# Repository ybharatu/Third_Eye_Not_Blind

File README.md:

# Third_Eye_Not_Blind 
Senior Design

Authors:
  - Yash Bharatula
  - Kyla Hayes
  - Michael Toner
- Alex Symanski

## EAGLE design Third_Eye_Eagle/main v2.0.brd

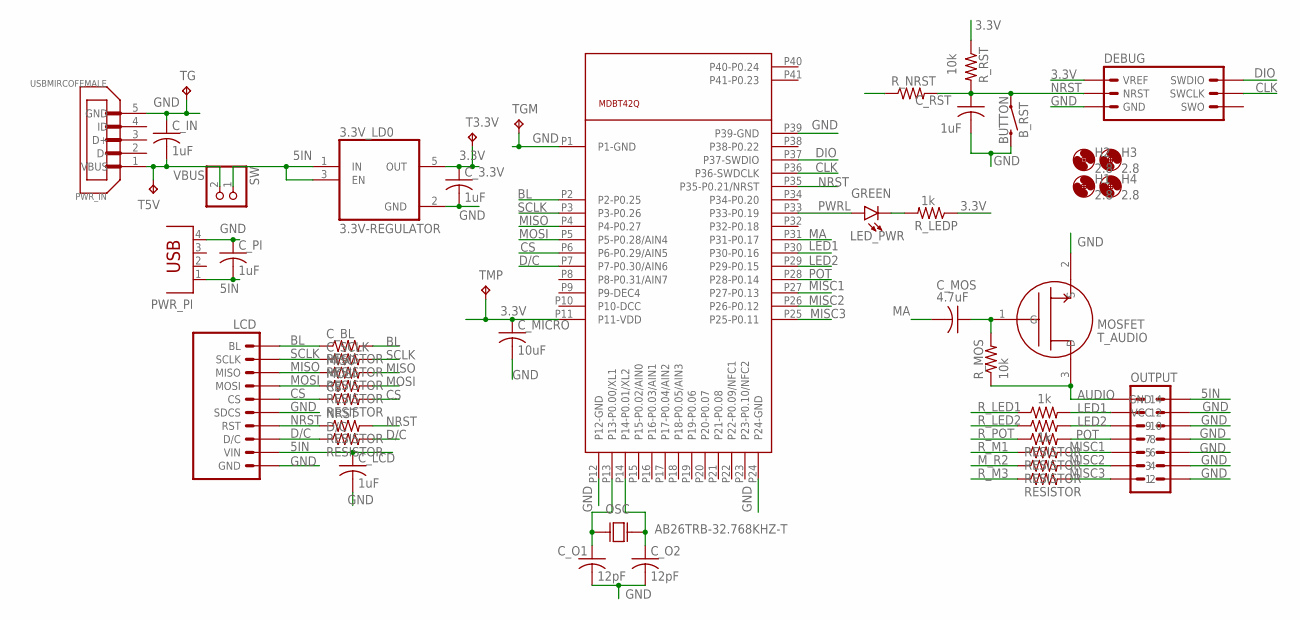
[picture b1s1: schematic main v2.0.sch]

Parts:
3.3V_LD0: 3.3V-REGULATOR; SOT95P280X145-5N
B_RST: BUTTON; TACTILE_SWITCH_SMD_6.2MM_TALL
CS: RESISTOR; R0805
C_3.3V: 1uF; C0805
C_BL: RESISTOR; R0805
C_IN: 1uF; C0805
C_LCD: 1uF; C0805
C_MICRO: 10uF; C0805
C_MOS: 4.7uF; C0805
C_O1, C_O2: 12pF; C0805
C_PI: 1uF; C0805
C_RST: 1uF; C0805
C_SCLK: RESISTOR; R0805
D/C: RESISTOR; R0805
DEBUG: DEBUGGER; MA03-2
H1, H2, H3, H4: 2.8; 2,8
LCD: LCDHEADERS; MA10-1
LED_PWR: GREEN; LED-1206
MISO: RESISTOR; R0805
MOSI: RESISTOR; R0805
M_R2: RESISTOR; R0805
NRST: RESISTOR; R0805
OSC: AB26TRB-32.768KHZ-T; XTAL_AB26TRB-32.768KHZ-T
OUTPUT: OUTHEADER; MA07-2
PWR_IN: USBMIRCOFEMALE; MOLEX_0473460001
PWR_PI: USBCON; PN87520
R_LED1, R_LED2: 1k; R0805
R_LEDP: 1k; R0805
R_M1, R_M3: RESISTOR; R0805
R_MOS: 10k; R0805
R_NRST: RESISTOR; R0805
R_POT: RESISTOR; R0805
R_RST: 10k; R0805
SW: PINHD-1X2; 1X02
T3.3V, T5V: TPTP11SQ; TP11SQ
TG: TPTP11SQ; TP11SQ
TGM: TPTP11SQ; TP11SQ
TMP: TPTP11SQ; TP11SQ
T_AUDIO: MOSFET; SOT23
U$1: MDBT42Q; MDBT40

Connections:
3.3V: 3.3V_LD0.5 (OUT), C_3.3V.1, C_MICRO.1, DEBUG.6 (VREF), R_LEDP.1, R_RST.1, T3.3V.TP, TMP.TP, U$1.P11 (P11-VDD)
5IN: 3.3V_LD0.1 (IN), 3.3V_LD0.3 (EN), C_LCD.1, C_PI.2, LCD.2 (VIN), OUTPUT.13 (GND), PWR_PI.1, SW.1
AUDIO: OUTPUT.14, R_MOS.1, T_AUDIO.3 (D)
BL: C_BL.1, C_BL.2, LCD.10 (BL), U$1.P2 (P2-P0.25)
CLK: DEBUG.3 (SWCLK), U$1.P36 (P36-SWDCLK)
CS: CS.1, CS.2, LCD.6 (CS), U$1.P6 (P6-P0.29/AIN5)
D/C: D/C.1, D/C.2, LCD.3 (D/C), U$1.P7 (P7-P0.30/AIN6)
DIO: DEBUG.5 (SWDIO), U$1.P37 (P37-SWDIO)
GND: 3.3V_LD0.2 (GND), B_RST.B1 (2), B_RST.B2 (2), C_3.3V.2, C_IN.1, C_LCD.2, C_MICRO.2, C_O1.2, C_O2.2, C_PI.1, C_RST.2, DEBUG.2 (GND), LCD.1 (GND), LCD.5 (SDCS), OUTPUT.1, OUTPUT.3, OUTPUT.5, OUTPUT.7, OUTPUT.9, OUTPUT.11 (VCC), PWR_IN.5 (GND), PWR_PI.4, TG.TP, TGM.TP, T_AUDIO.2 (S), U$1.P1 (P1-GND), U$1.P12 (P12-GND), U$1.P24 (P24-GND), U$1.P39 (P39-GND)
LED1: OUTPUT.12, R_LED1.1, R_LED1.2, U$1.P30 (P30-P0.16)
LED2: OUTPUT.10, R_LED2.1, R_LED2.2, U$1.P29 (P29-P0.15)
MA: C_MOS.2, U$1.P31 (P31-P0.17)
MISC1: OUTPUT.6, R_M1.1, R_M1.2, U$1.P27 (P27-P0.13)
MISC2: M_R2.1, M_R2.2, OUTPUT.4, U$1.P26 (P26-P0.12)
MISC3: OUTPUT.2, R_M3.1, R_M3.2, U$1.P25 (P25-P0.11)
MISO: LCD.8 (MISO), MISO.1, MISO.2, U$1.P4 (P4-P0.27)
MOSI: LCD.7 (MOSI), MOSI.1, MOSI.2, U$1.P5 (P5-P0.28/AIN4)
unnamed: C_O1.1, OSC.1, U$1.P13 (P13-P0.00/XL1)
unnamed: C_O2.1, OSC.2, U$1.P14 (P14-P0.01/XL2)
unnamed: C_MOS.1, R_MOS.2, T_AUDIO.1 (G)
unnamed: LED_PWR.C, R_LEDP.2
NRST: B_RST.A1 (1), B_RST.A2 (1), C_RST.1, DEBUG.4 (NRST), LCD.4 (RST), NRST.1, NRST.2, R_NRST.1, R_NRST.2, R_RST.2, U$1.P35 (P35-P0.21/NRST)
POT: OUTPUT.8, R_POT.1, R_POT.2, U$1.P28 (P28-P0.14)
PWRL: LED_PWR.A, U$1.P33 (P33-P0.19)
SCLK: C_SCLK.1, C_SCLK.2, LCD.9 (SCLK), U$1.P3 (P3-P0.26)
VBUS: C_IN.2, PWR_IN.1 (VBUS), SW.2, T5V.TP

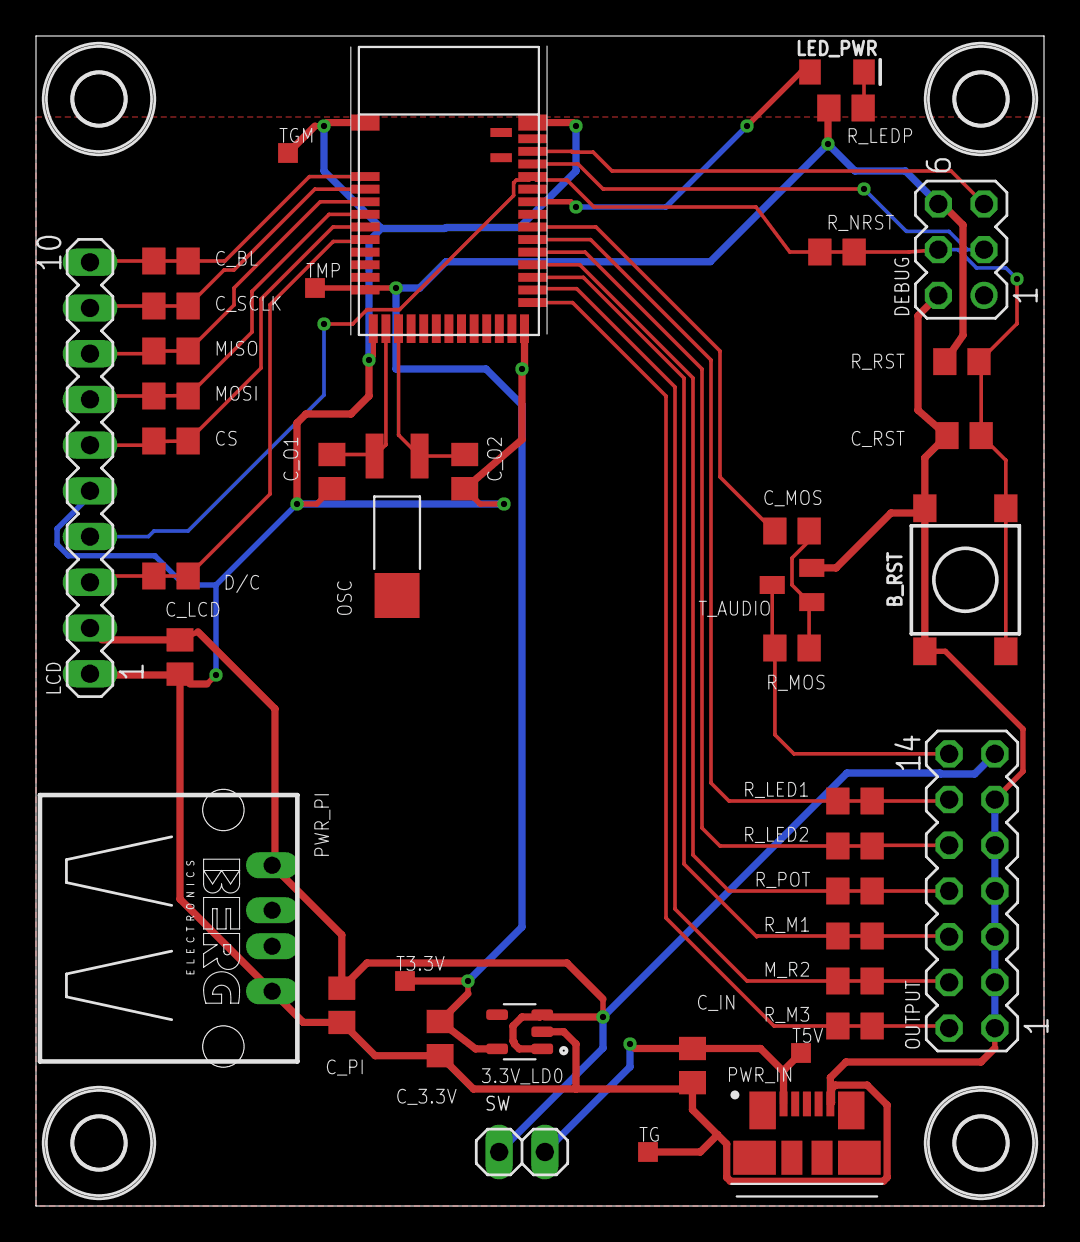
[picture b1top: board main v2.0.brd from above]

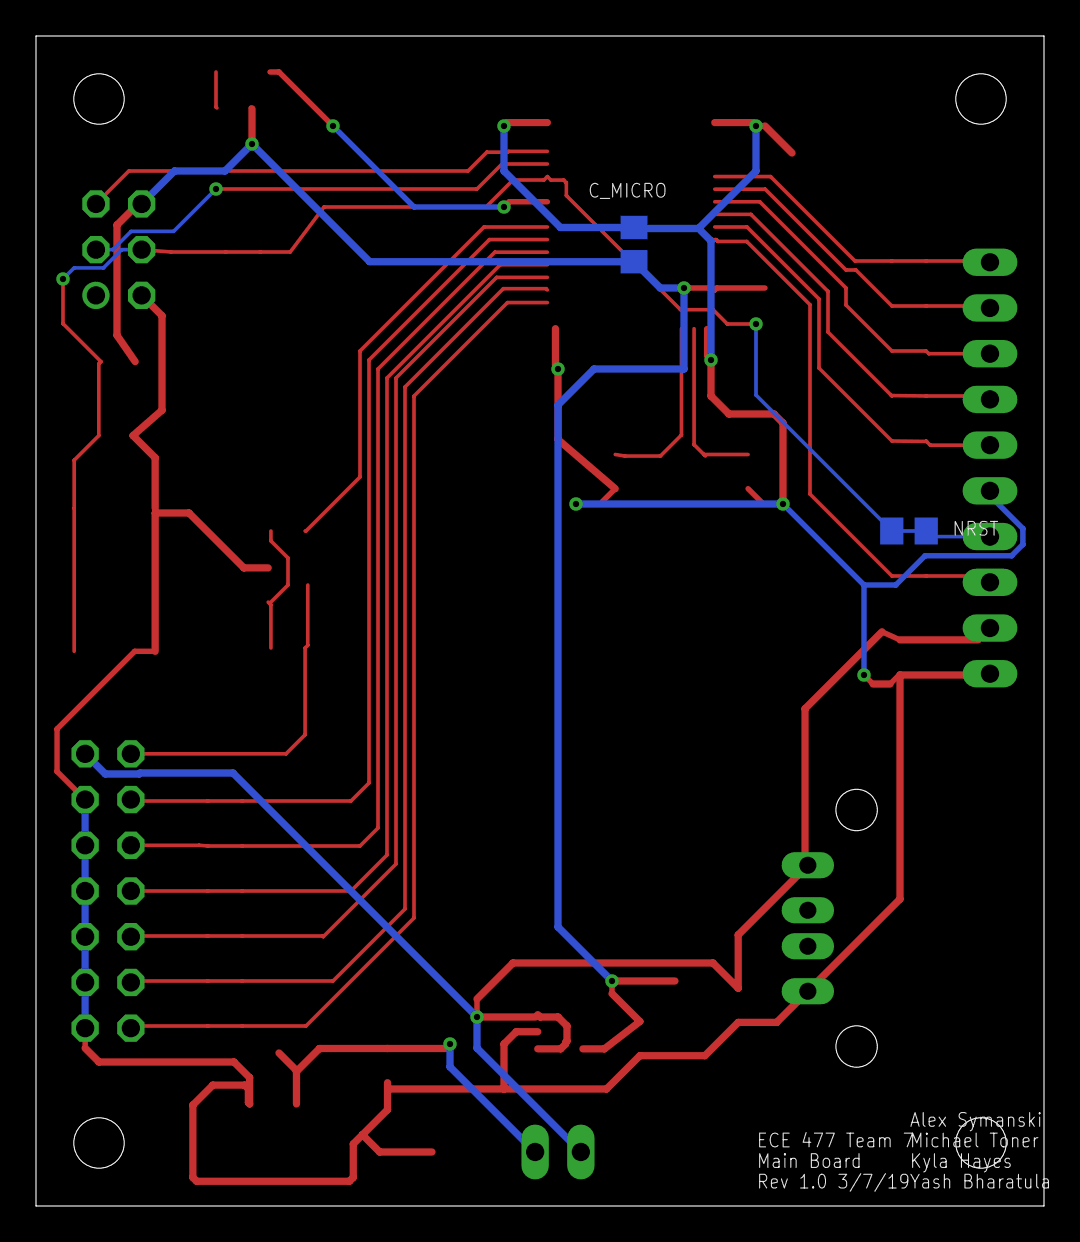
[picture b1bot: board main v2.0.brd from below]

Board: 2 copper layers, 56.0 x 65.0 mm, 47 parts (2 on the bottom side), 26 nets.

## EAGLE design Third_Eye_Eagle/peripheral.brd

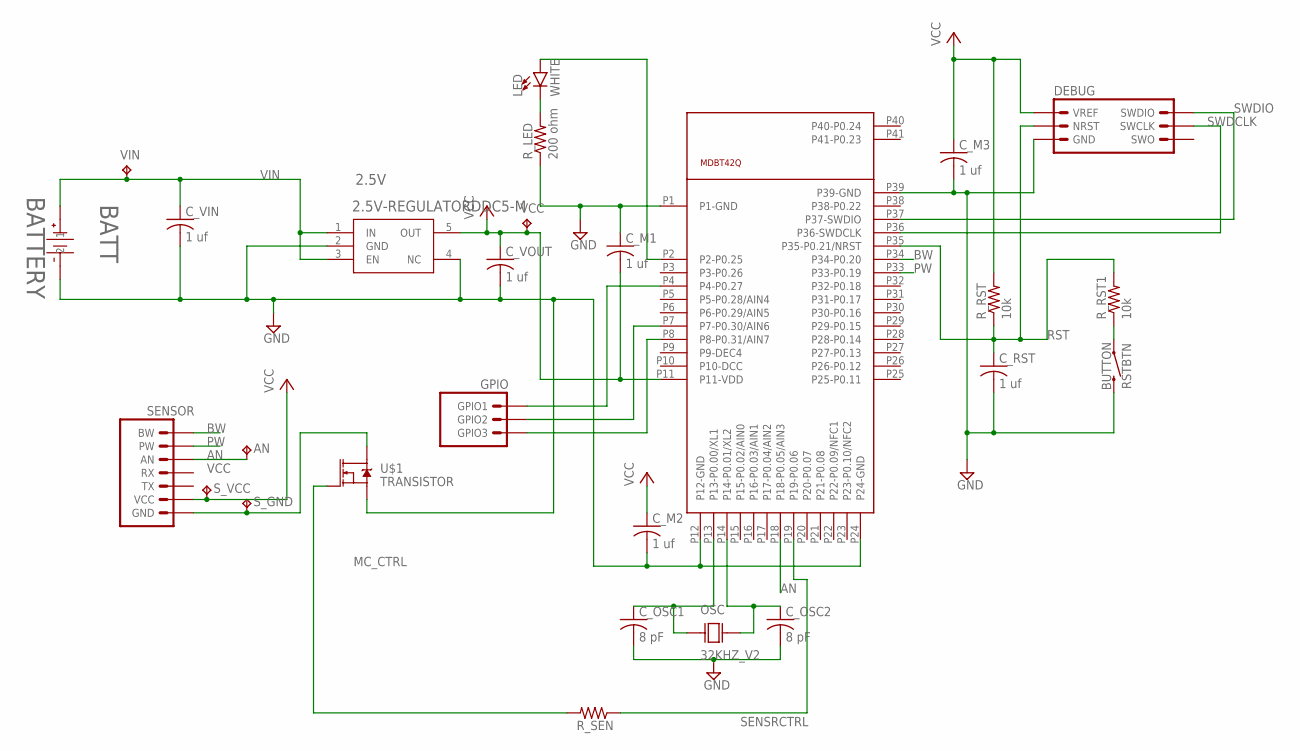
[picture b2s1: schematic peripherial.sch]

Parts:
2.5V: 2.5V-REGULATORDDC5-M; DDC5-M
AN: TPTP11SQ; TP11SQ
BATT: BATTERY; BAT_HLDR_2468
C_M1, C_M2, C_M3: 1 uf; C0805K
C_OSC1, C_OSC2: 8 pF; C0805K
C_RST: 1 uf; C0805K
C_VIN: 1 uf; C0805K
C_VOUT: 1 uf; C0805K
DEBUG: DEBUGGER; MA03-2
GPIO: GPIO; MA03-1
LED: WHITE; LED-1206
MICRO: MDBT42Q; MDBT40
OSC: 32KHZ_V2; XTAL_AB26TRB-32.768KHZ-T
RSTBTN: BUTTON; TACTILE_SWITCH_SMD_6.2MM_TALL
R_LED: 200 ohm; M0805
R_RST, R_RST1: 10k; M0805
R_SEN: RESISTOR; M0805
SENSOR: SENSORHEADER; MA07-1
S_GND: TPTP11SQ; TP11SQ
S_VCC: TPTP11SQ; TP11SQ
U$1: TRANSISTOR; SOT23-3
VCC: TPTP11SQ; TP11SQ
VIN: TPTP11SQ; TP11SQ

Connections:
AN: AN.TP, MICRO.P18 (P18-P0.05/AIN3), SENSOR.5 (AN)
BW: MICRO.P34 (P34-P0.20), SENSOR.7 (BW)
GND: 2.5V.2 (GND), 2.5V.4 (NC), BATT.2, BATT.3 (2), BATT.4 (2), C_M1.1, C_M2.2, C_M3.2, C_OSC1.2, C_OSC2.2, C_RST.2, C_VIN.2, C_VOUT.2, DEBUG.2 (GND), MICRO.P1 (P1-GND), MICRO.P12 (P12-GND), MICRO.P24 (P24-GND), MICRO.P39 (P39-GND), RSTBTN.TOP1 (2), RSTBTN.TOP2 (2), R_LED.1, U$1.2_S (S)
MC_CTRL: R_SEN.2, U$1.1_G (G)
unnamed: C_OSC1.1, MICRO.P13 (P13-P0.00/XL1), OSC.P$3 (1)
unnamed: LED.C, R_LED.2
unnamed: C_OSC2.1, MICRO.P14 (P14-P0.01/XL2), OSC.P$4 (2)
unnamed: SENSOR.1 (GND), S_GND.TP, U$1.3_D (D)
unnamed: LED.A, MICRO.P2 (P2-P0.25)
unnamed: RSTBTN.BOTTOM1 (1), RSTBTN.BOTTOM2 (1), R_RST1.1
unnamed: GPIO.1 (GPIO3), MICRO.P8 (P8-P0.31/AIN7)
unnamed: GPIO.2 (GPIO2), MICRO.P7 (P7-P0.30/AIN6)
unnamed: GPIO.3 (GPIO1), MICRO.P4 (P4-P0.27)
PW: MICRO.P33 (P33-P0.19), SENSOR.6 (PW)
RST: C_RST.1, DEBUG.4 (NRST), MICRO.P35 (P35-P0.21/NRST), R_RST.1, R_RST1.2
SENSRCTRL: MICRO.P19 (P19-P0.06), R_SEN.1
SWDCLK: DEBUG.3 (SWCLK), MICRO.P36 (P36-SWDCLK)
SWDIO: DEBUG.5 (SWDIO), MICRO.P37 (P37-SWDIO)
VCC: 2.5V.5 (OUT), C_M1.2, C_M2.1, C_M3.1, C_VOUT.1, DEBUG.6 (VREF), MICRO.P11 (P11-VDD), R_RST.2, SENSOR.2 (VCC), S_VCC.TP, VCC.TP
VIN: 2.5V.1 (IN), 2.5V.3 (EN), BATT.1, C_VIN.1, VIN.TP

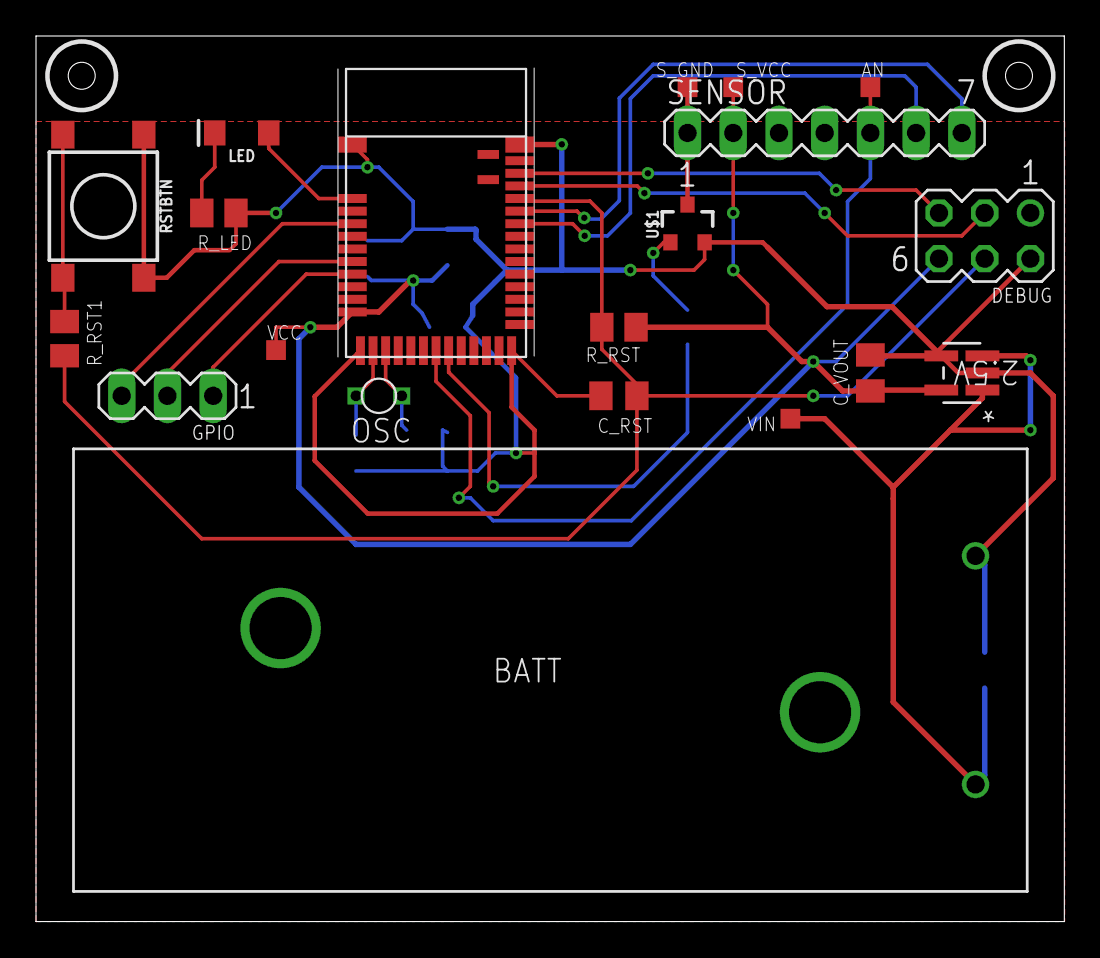
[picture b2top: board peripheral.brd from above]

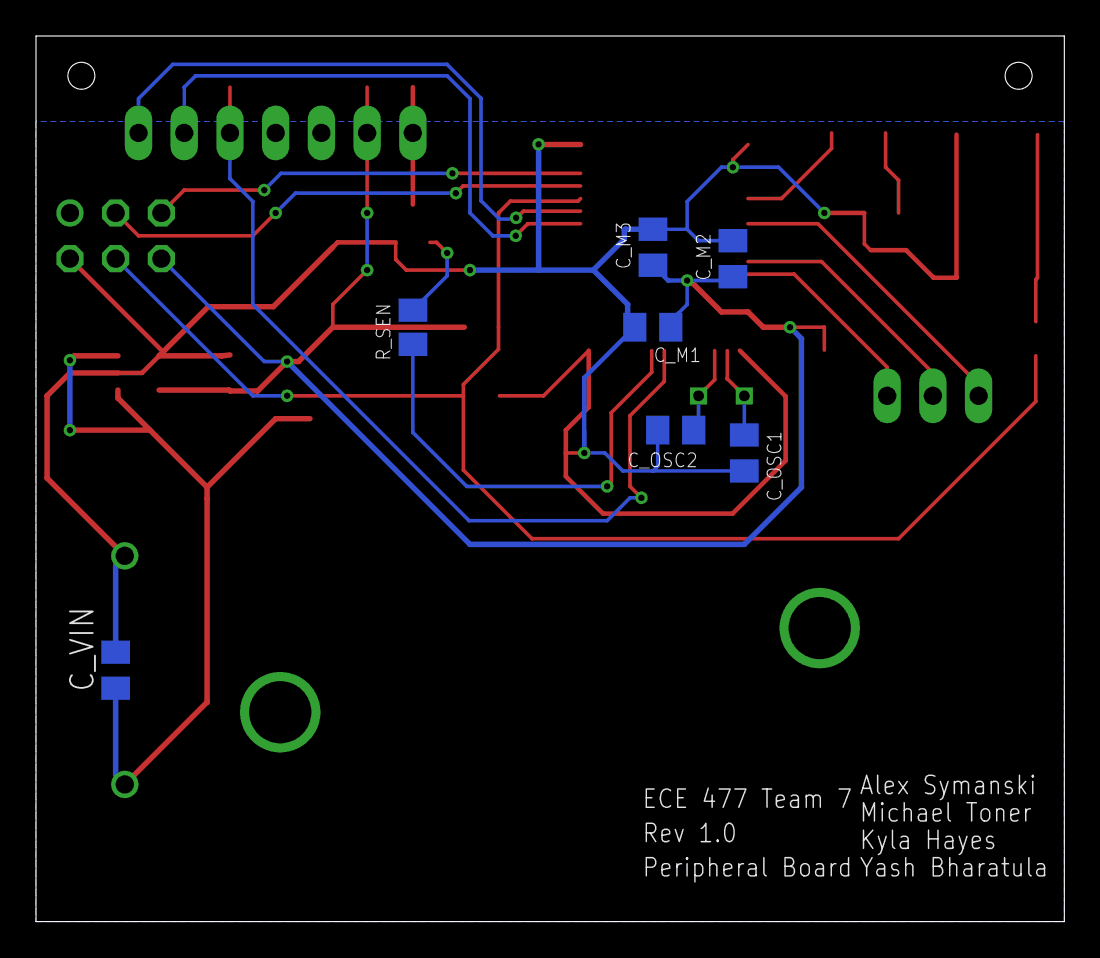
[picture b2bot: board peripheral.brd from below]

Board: 2 copper layers, 57.1 x 49.2 mm, 27 parts (7 on the bottom side), 20 nets.

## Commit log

2019-01-11 Lane Detection Algorithm
2019-01-11 Fixed Readme
2019-01-16 Test Commit Michael
2019-01-16 Adding img buf objects and testing with them
2019-01-16 Setting up thread
2019-01-16 Trying to use Queue Class
2019-01-17 Queue class and multithreading working but now its slower so thats cool
2019-01-23 Added Alex
2019-01-23 Changed README format
2019-01-23 This is not as fun on a windows
2019-01-23 video to images
2019-01-23 hashtag
2019-01-25 New Algorithm
2019-01-28 Added Timing Measurements
2019-01-28 Added multicore functionality
2019-01-28 added test_images to gitignore
2019-01-28 Removed test images
2019-01-28 modified to do video
2019-02-02 Apparently i have to commit this image to my branch to checkout yash's
2019-02-05 just testing the code on yash's branch
2019-02-06 Uploaded Inventor Part Files
2019-02-08 make sure
2019-02-08 Cleaned up Code
2019-02-08 still hanging at img 98
2019-02-11 fixed yellow color mask
2019-02-11 Adding Eagle_Library
2019-02-12 Ultrasonic Code Snippet
2019-02-12 cleaned up files and added video flag
2019-02-12 forgot to add processed_images to the gitignore
2019-02-12 fixed hanging issue caused by image_buffer being too full
2019-02-13 updating eagle library
2019-02-13 Fixing Eagle Project Structure
2019-02-13 added middle line
2019-02-13 Modified lane_detect.py
2019-02-13 modified output to be drift status on output buffer
2019-02-13 Untested Parallel Architecture implemented
2019-02-13 Integrated Changes, but does not work
2019-02-13 Updated Eagle LIbrary and git ignore the eagle temp files
2019-02-13 Put the inventor files into seperate directory
2019-02-14 Multiprocessing works on laptop
2019-02-14 Eagle library updates and schematic changes
2019-02-15 Improved multicore performance on raspberry
2019-02-15 Finished the peripherial schematic
2019-02-15 Alex additions to Eagle library and main schematic
2019-02-15 My new branch
2019-02-15 Updating eagle library again to merge with alex
2019-02-20 fixing conflicts in lane_Detect
2019-02-21 resized and cropped image
2019-02-22 Uploaded main.c and sdk_config.c
2019-02-25 added code to save images for debugging
2019-02-25 Serial Image Processing with smaller image size
2019-03-01 2 worker threads
2019-03-01 added function to print images for testing
2019-03-01 just changed process image to use houghlines2
2019-03-04 added live arg
2019-03-04 commented out filename print
2019-03-04 filename = livefeed
2019-03-04 camera_test_save working with 23fps
2019-03-04 combining working live feed with working lane detection code
2019-03-06 piimage added
2019-03-06 code from show me a thing
2019-03-06 image option and save option and roi
2019-03-06 checked code still works with challenge vid
2019-03-06 counter in live image handler was global counter
2019-03-18 live feed working
2019-03-18 gitignore
2019-03-18 gitignore extra random files on pi
2019-03-20 Adding sdk config
2019-03-21 files to demonstrate live feed works
2019-03-24 Added Peripheral Micro Code
2019-03-24 Peripheral Functionality implemented
2019-03-25 Blind Spot Detection Code Working
2019-03-25 Created Main Micro Folder
2019-03-25 deleting yash's mistakes
2019-03-25 Adding main micro main and sdk config files to github
2019-03-25 Cleaned up peripheral_micro main.c
2019-03-25 Minor Cleanup to main micro main.c
2019-03-25 removing an old main sdk_config file
2019-03-25 Adding peripherial brd and sch files to git
2019-03-25 Removing unnecessary files from master
2019-03-25 Adding the eagle project file to gitignore
2019-03-25 adding and removing unncessary eagle files from git
2019-03-25 adding cam outputs to git ignore
2019-03-25 Rename peripherial to peripheral, the correct spelling
2019-03-25 Removed eagle file from git and tweaked the main micro code
2019-03-25 Added GPIO code
2019-03-26 restructured code
2019-03-26 deleted some old files hopefully no one needs
2019-03-27 Code verified with live video
2019-03-27 changed gitignore
2019-03-28 main unit inventor file measured
2019-03-28 ready to print
    not sure what the package file is
2019-03-29 added led holes
2019-04-02 about 10 FPS on live
2019-04-03 Added Test Videos
2019-04-03 Add files via upload
    Final main board schematic and board layout
2019-04-03 playing with houghlines and canny thresholds
2019-04-05 adding code snippet for lanes and bluetooth symbol
2019-04-07 Swapping central and peripheral roles and adding features
2019-04-07 Same as other commit
2019-04-10 working on thresholds and about to change list to queue
2019-04-15 Updated main micro code to include PWM
2019-04-15 Updated config to allow for PWM
2019-04-15 LCD displays 2 bluetooth logos
2019-04-15 Peripheral micro changes?
2019-04-17 video working with lane departure, need to test live and no save version
2019-04-17 working without save flag - should test on pi
2019-04-18 gpio updated
2019-04-22 made changes to live video ready to test
2019-04-22 live video working except for roi and cropping that will be adjusted later
2019-04-23 live video kinda working
2019-04-23 Fixed a type on filename
2019-04-24 Works for demo
2019-05-02 Finished main micro code
2019-05-02 Finished SDK Config for main micro
2019-05-02 Finished Peripheral micro code
2019-05-02 Finished Peripheral SDK Config
